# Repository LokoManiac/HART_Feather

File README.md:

# HART_Feather
HART communication system built into the Adafruit Feather format

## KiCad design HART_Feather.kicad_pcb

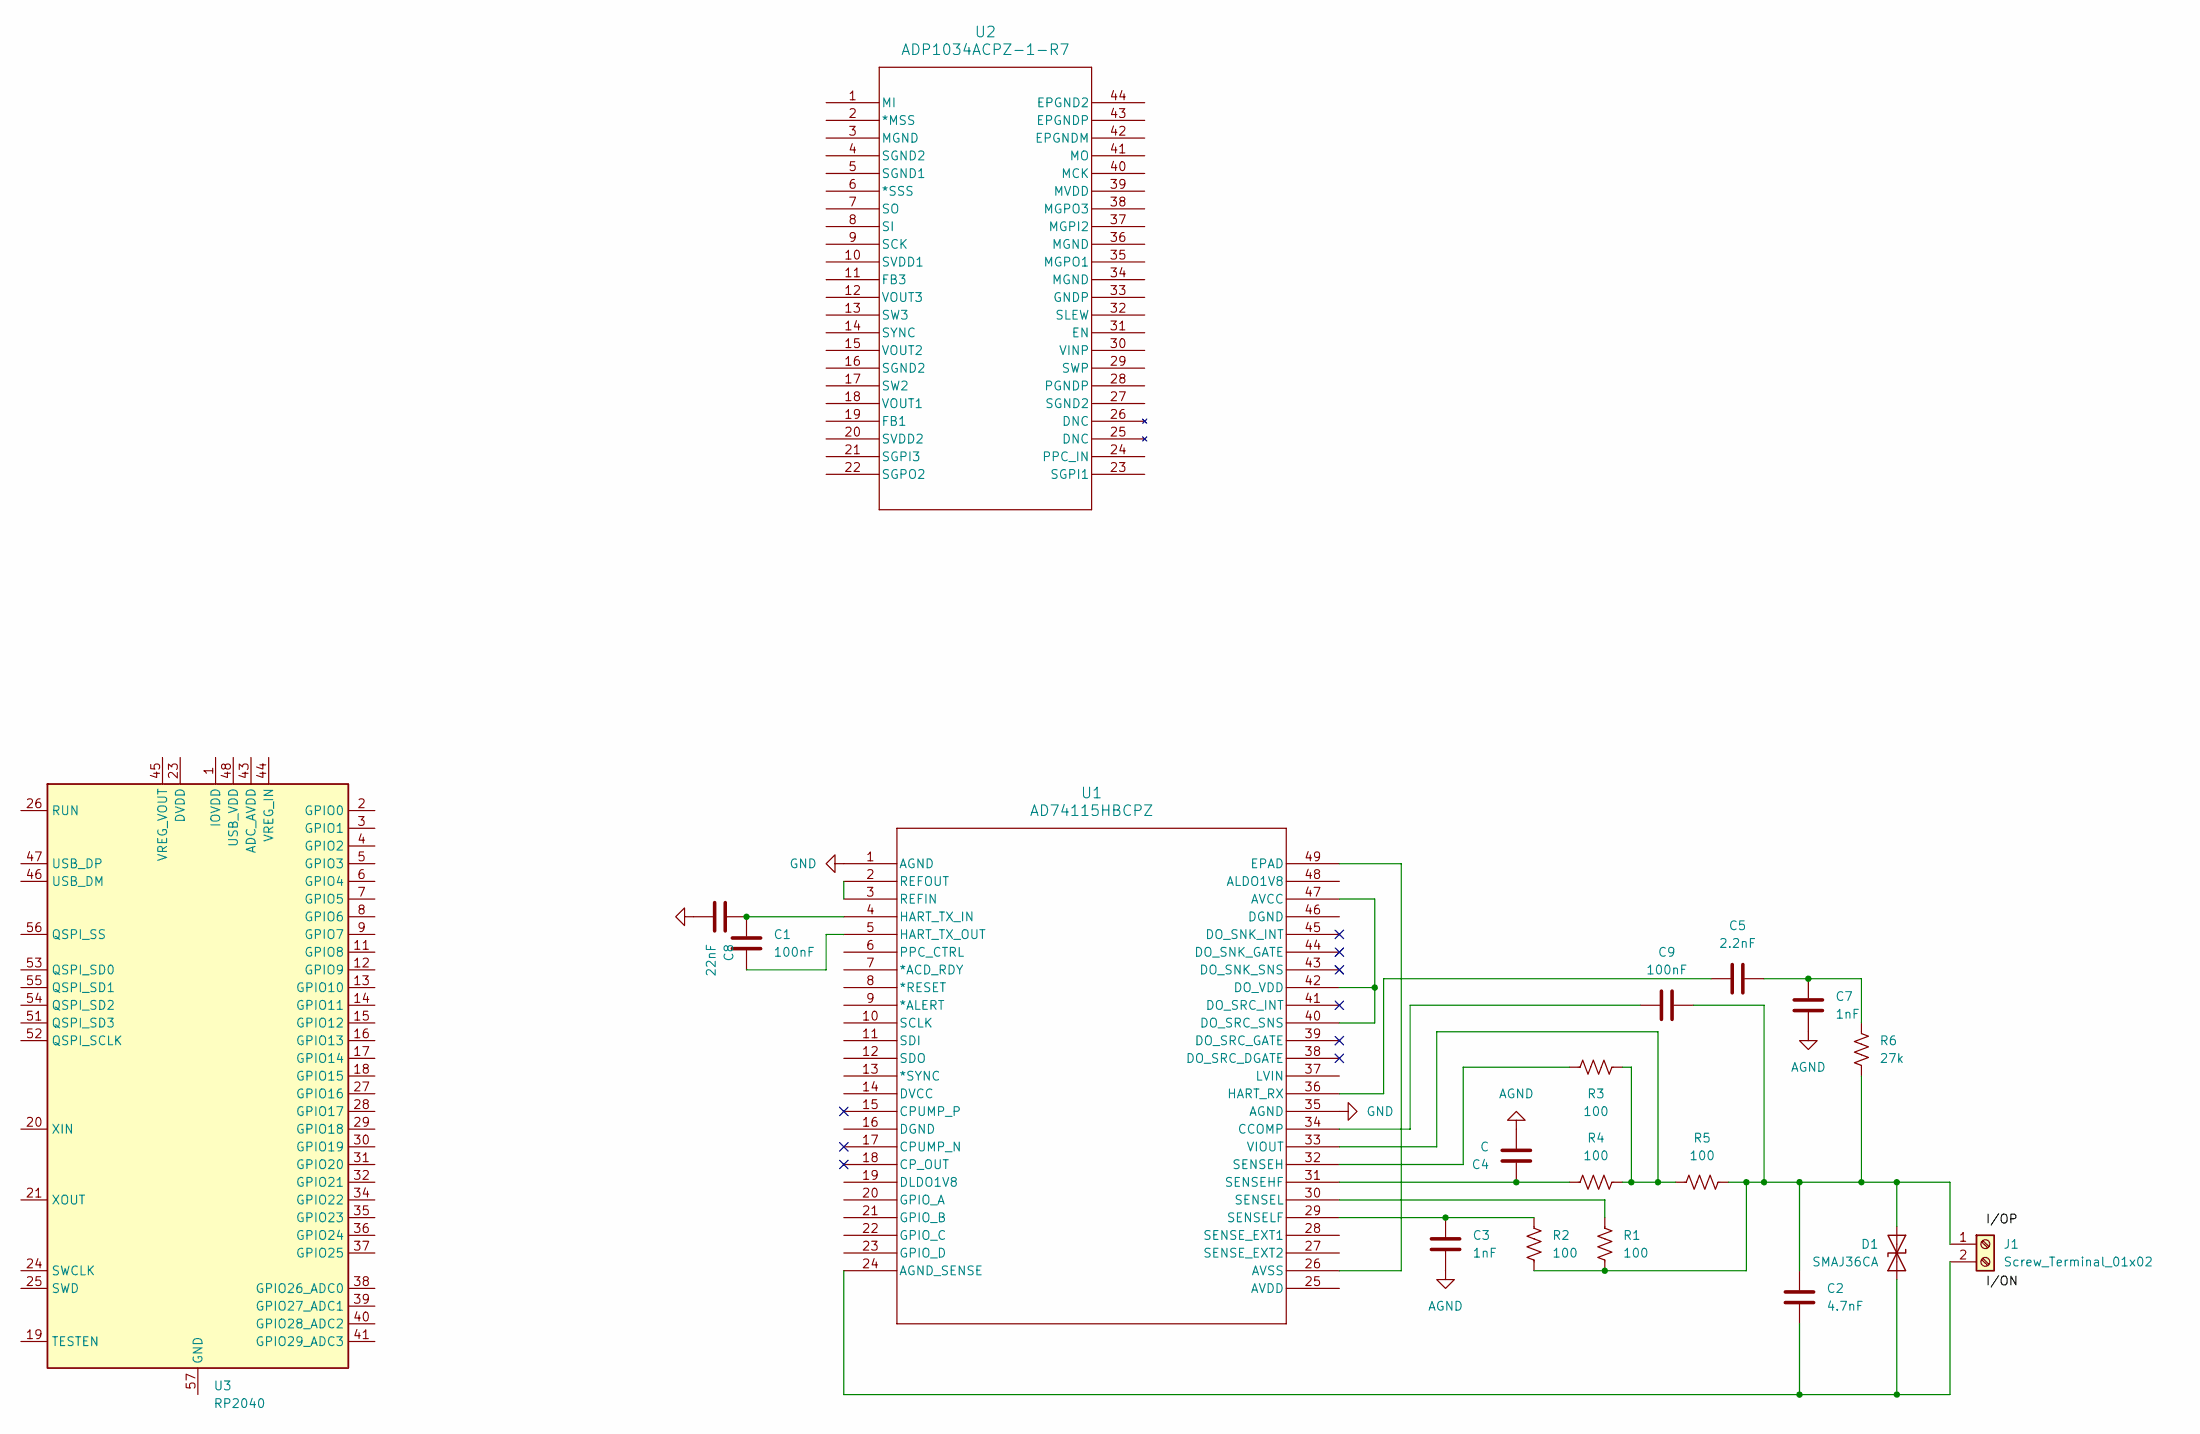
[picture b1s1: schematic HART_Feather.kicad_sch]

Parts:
C1, C9: 100nF; CP_EIA-1608-08_AVX-J
C2: 4.7nF; CP_EIA-1608-08_AVX-J
C3, C7: 1nF; CP_EIA-1608-08_AVX-J
C4: C; CP_EIA-1608-08_AVX-J
C5: 2.2nF; R_0201_0603Metric
C8: 22nF; CP_EIA-1608-08_AVX-J
D1: SMAJ36CA; D_SMA
J1: Screw_Terminal_01x02
R1, R2, R3, R4, R5: 100; R_0201_0603Metric
R6: 27k; R_0201_0603Metric
U1: AD74115HBCPZ; CP-48-28_ADI
U2: ADP1034ACPZ-1-R7; CP-41-1_ADI
U3: RP2040; QFN-56-1EP_7x7mm_P0.4mm_EP3.2x3.2mm

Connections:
AGND: C3.2, C4.2, C7.2
GND: C8.2, U1.1 (AGND), U1.35 (AGND)
unnamed: C5.2, C7.1, R6.2
unnamed: C2.1, D1.1 (A1), J1.2, U1.24 (AGND_SENSE)
unnamed: C2.2, C9.2, D1.2 (A2), J1.1, R1.2, R2.2, R5.2, R6.1
unnamed: U1.40 (DO_SRC_SNS), U1.42 (DO_VDD), U1.47 (AVCC)
unnamed: U1.26 (AVSS), U1.49 (EPAD)
unnamed: C9.1, U1.34 (CCOMP)
unnamed: C5.1, U1.36 (HART_RX)
unnamed: C1.1, C8.1, U1.4 (HART_TX_IN)
unnamed: C1.2, U1.5 (HART_TX_OUT)
unnamed: U1.2 (REFOUT), U1.3 (REFIN)
unnamed: R3.1, U1.32 (SENSEH)
unnamed: C4.1, R4.1, U1.31 (SENSEHF)
unnamed: R1.1, U1.30 (SENSEL)
unnamed: C3.1, R2.1, U1.29 (SENSELF)
unnamed: R3.2, R4.2, R5.1, U1.33 (VIOUT)
unnamed: U3.23 (DVDD), U3.50 (DVDD)
unnamed: U3.1 (IOVDD), U3.10 (IOVDD), U3.22 (IOVDD), U3.33 (IOVDD), U3.42 (IOVDD), U3.49 (IOVDD)

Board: 2 copper layers, 18 parts (0 on the bottom side), 19 nets, no tracks yet.

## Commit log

2025-01-06 Initial Upload
2025-01-06 test remote commit
2025-01-14 Backup
